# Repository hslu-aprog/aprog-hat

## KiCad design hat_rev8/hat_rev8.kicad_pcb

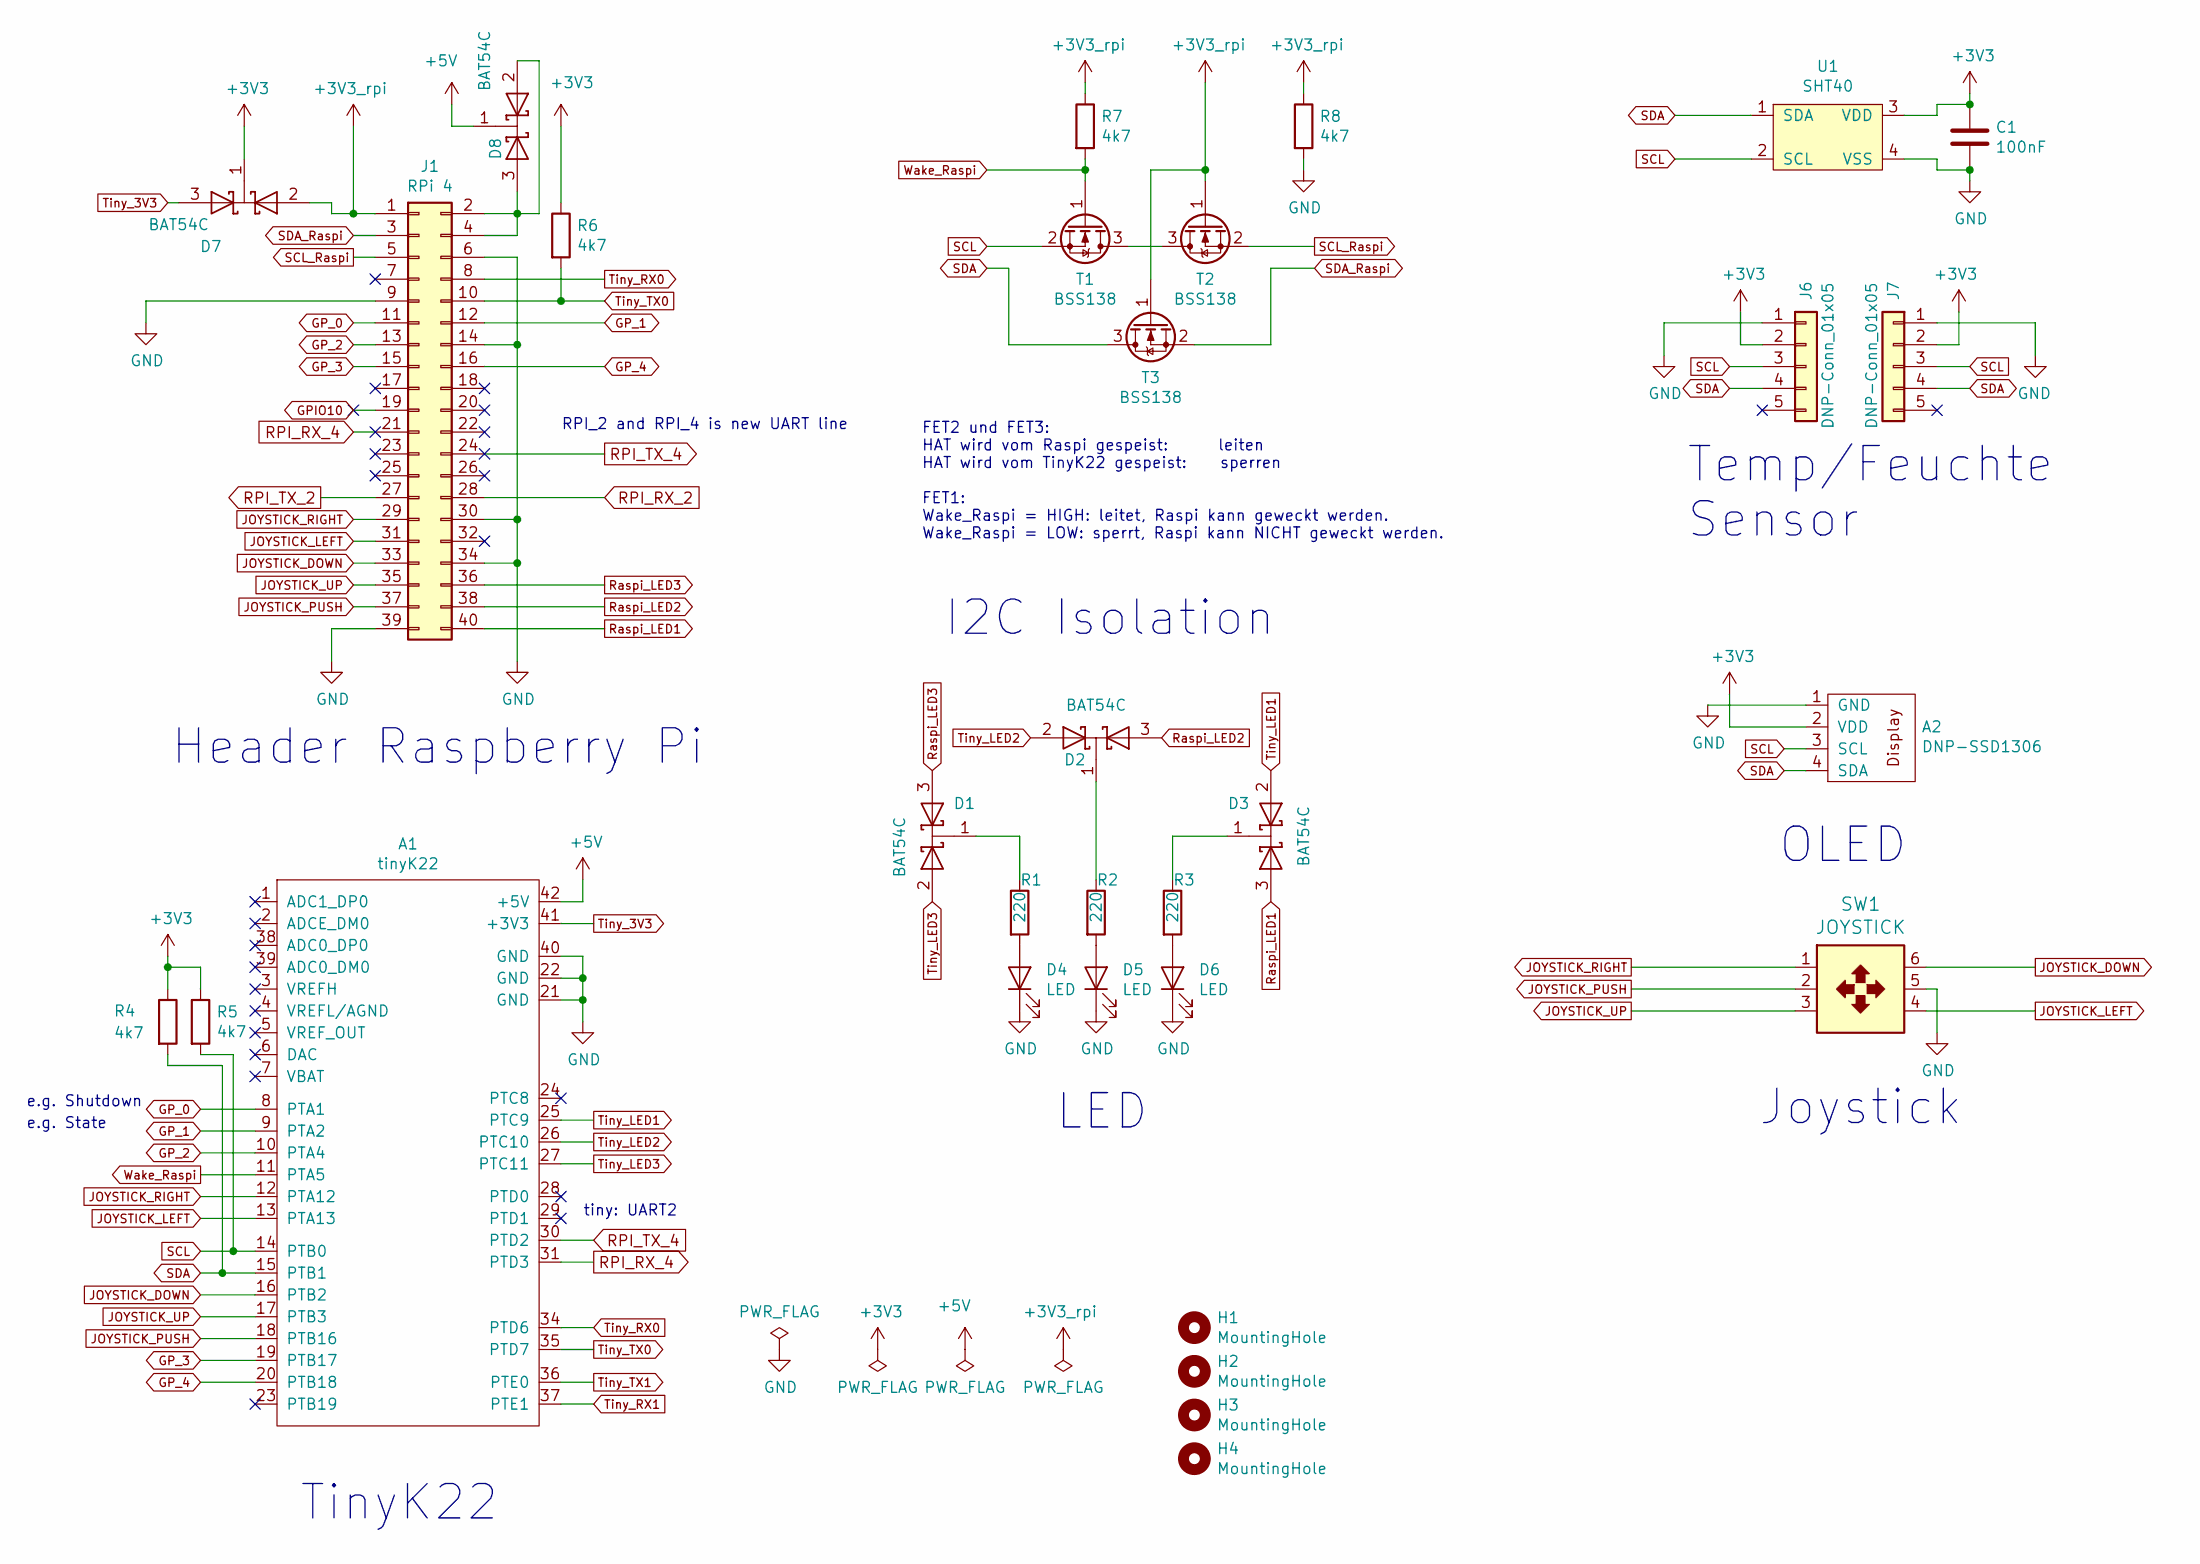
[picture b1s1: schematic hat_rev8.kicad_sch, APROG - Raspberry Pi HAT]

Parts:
A1: tinyK22
A2: DNP-SSD1306; SSD1306
C1: 100nF; C_0805_2012Metric
D1, D2, D3, D7, D8: BAT54C; D_SOT-23_ANK
D4, D5, D6: LED; LED_D3.0mm
H1, H2, H3, H4: MountingHole; MountingHole_2.7mm_M2.5_ISO7380_Pad
J1: RPi 4; PinHeader_2x20_P2.54mm_Vertical
J6, J7: DNP-Conn_01x05; PinHeader_1x05_P2.54mm_Vertical
R1, R2, R3: 220; R_0805_2012Metric
R4, R5, R6, R7, R8: 4k7; R_0805_2012Metric
SW1: JOYSTICK; Joystick
T1, T2, T3: BSS138; SOT-23
U1: SHT40

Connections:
+3V3: A2.2 (VDD), C1.1, D7.1 (K), J6.2, J7.2, R4.1, R5.1, R6.1, U1.3 (VDD)
+3V3_rpi: D7.2 (A), J1.1, R7.1, R8.1, T2.1 (G), T3.1 (G)
+5V: A1.42 (+5V), D8.1 (K)
GND: A1.21 (GND), A1.22 (GND), A1.40 (GND), A2.1 (GND), C1.2, D4.1 (K), D5.1 (K), D6.1 (K), J1.6, J1.9, J1.14, J1.30, J1.34, J1.39, J6.1, J7.1, R8.2, SW1.5, U1.4 (VSS)
GPIO10: J1.19
GP_0: A1.8 (PTA1), J1.11
GP_1: A1.9 (PTA2), J1.12
GP_2: A1.10 (PTA4), J1.13
GP_3: A1.19 (PTB17), J1.15
GP_4: A1.20 (PTB18), J1.16
JOYSTICK_DOWN: A1.16 (PTB2), J1.33, SW1.6
JOYSTICK_LEFT: A1.13 (PTA13), J1.31, SW1.4
JOYSTICK_PUSH: A1.18 (PTB16), J1.37, SW1.2
JOYSTICK_RIGHT: A1.12 (PTA12), J1.29, SW1.1
JOYSTICK_UP: A1.17 (PTB3), J1.35, SW1.3
unnamed: D1.1 (K), R1.1
unnamed: D2.1 (K), R2.1
unnamed: D3.1 (K), R3.1
unnamed: D4.2 (A), R1.2
unnamed: D5.2 (A), R2.2
unnamed: D6.2 (A), R3.2
unnamed: D8.2 (A), D8.3 (A), J1.2, J1.4
unnamed: T1.3 (D), T2.3 (D)
RPI_RX_2: J1.28
RPI_RX_4: A1.31 (PTD3), J1.21
RPI_TX_2: J1.27
RPI_TX_4: A1.30 (PTD2), J1.24
Raspi_LED1: D3.3 (A), J1.40
Raspi_LED2: D2.3 (A), J1.38
Raspi_LED3: D1.3 (A), J1.36
SCL: A1.14 (PTB0), A2.3 (SCL), J6.3, J7.3, R5.2, T1.2 (S), U1.2 (SCL)
SCL_Raspi: J1.5, T2.2 (S)
SDA: A1.15 (PTB1), A2.4 (SDA), J6.4, J7.4, R4.2, T3.3 (D), U1.1 (SDA)
SDA_Raspi: J1.3, T3.2 (S)
Tiny_3V3: A1.41 (+3V3), D7.3 (A)
Tiny_LED1: A1.25 (PTC9), D3.2 (A)
Tiny_LED2: A1.26 (PTC10), D2.2 (A)
Tiny_LED3: A1.27 (PTC11), D1.2 (A)
Tiny_RX0: A1.34 (PTD6), J1.8
Tiny_RX1: A1.37 (PTE1)
Tiny_TX0: A1.35 (PTD7), J1.10, R6.2
Tiny_TX1: A1.36 (PTE0)
Wake_Raspi: A1.11 (PTA5), R7.2, T1.1 (G)

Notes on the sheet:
tiny: UART2
LED
Joystick
OLED
I2C Isolation
e.g. State
Temp/Feuchte Sensor
Header Raspberry Pi
FET2 und FET3: HAT wird vom Raspi gespeist: leiten HAT wird vom TinyK22 gespeist: sperren FET1: Wake_Raspi = HIGH: leitet, Raspi kann geweckt werden. Wake_Raspi = LOW: sperrt, Raspi kann NICHT geweckt werden.
e.g. Shutdown
TinyK22
RPI_2 and RPI_4 is new UART line

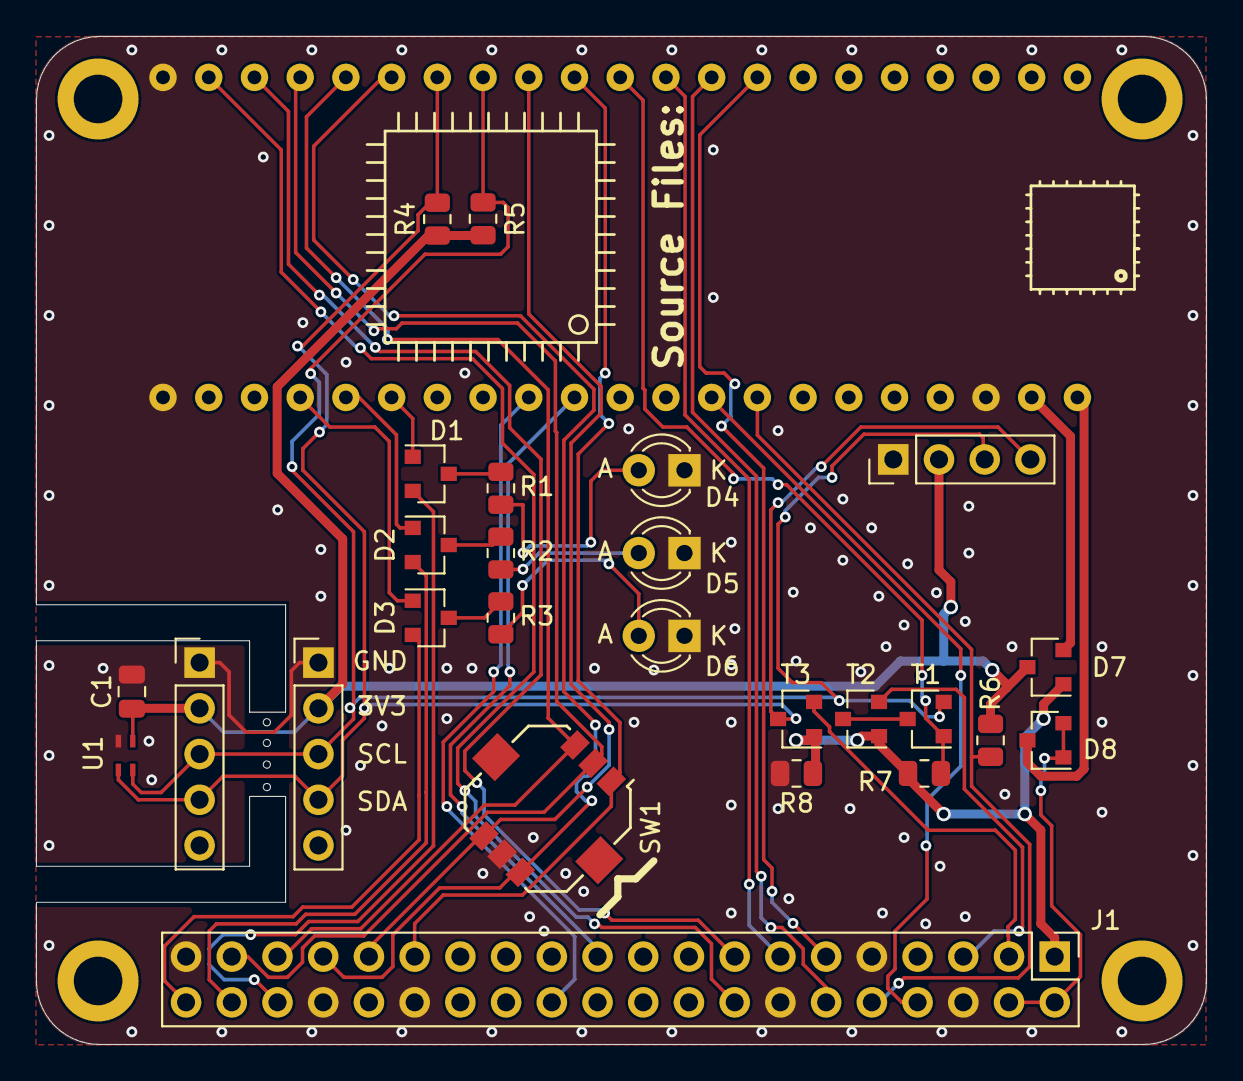
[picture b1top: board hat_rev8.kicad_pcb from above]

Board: 2 copper layers, 65.0 x 56.0 mm, 31 parts (0 on the bottom side), 38 nets.

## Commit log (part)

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2026-03-18 rename ibom to index
2026-03-18 update docs, remove old project file
2026-03-18 update documentation, provide link to repo
2026-03-18 change index title
2026-03-18 add kit contents picture
